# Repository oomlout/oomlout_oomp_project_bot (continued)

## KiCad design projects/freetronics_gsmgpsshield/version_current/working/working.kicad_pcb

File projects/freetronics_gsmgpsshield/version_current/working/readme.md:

# GSMGPSShield by freetronics  
This is a harvested standardized copy of a project from github.  
The original project can be found at:  
https://github.com/freetronics/GSMGPSShield  
Please consult that link for additional, details, files, and license information.  
Note: It was auto harvested and if the original repo had more than one board file or anything out of the ordinary the files here are likely not representative.

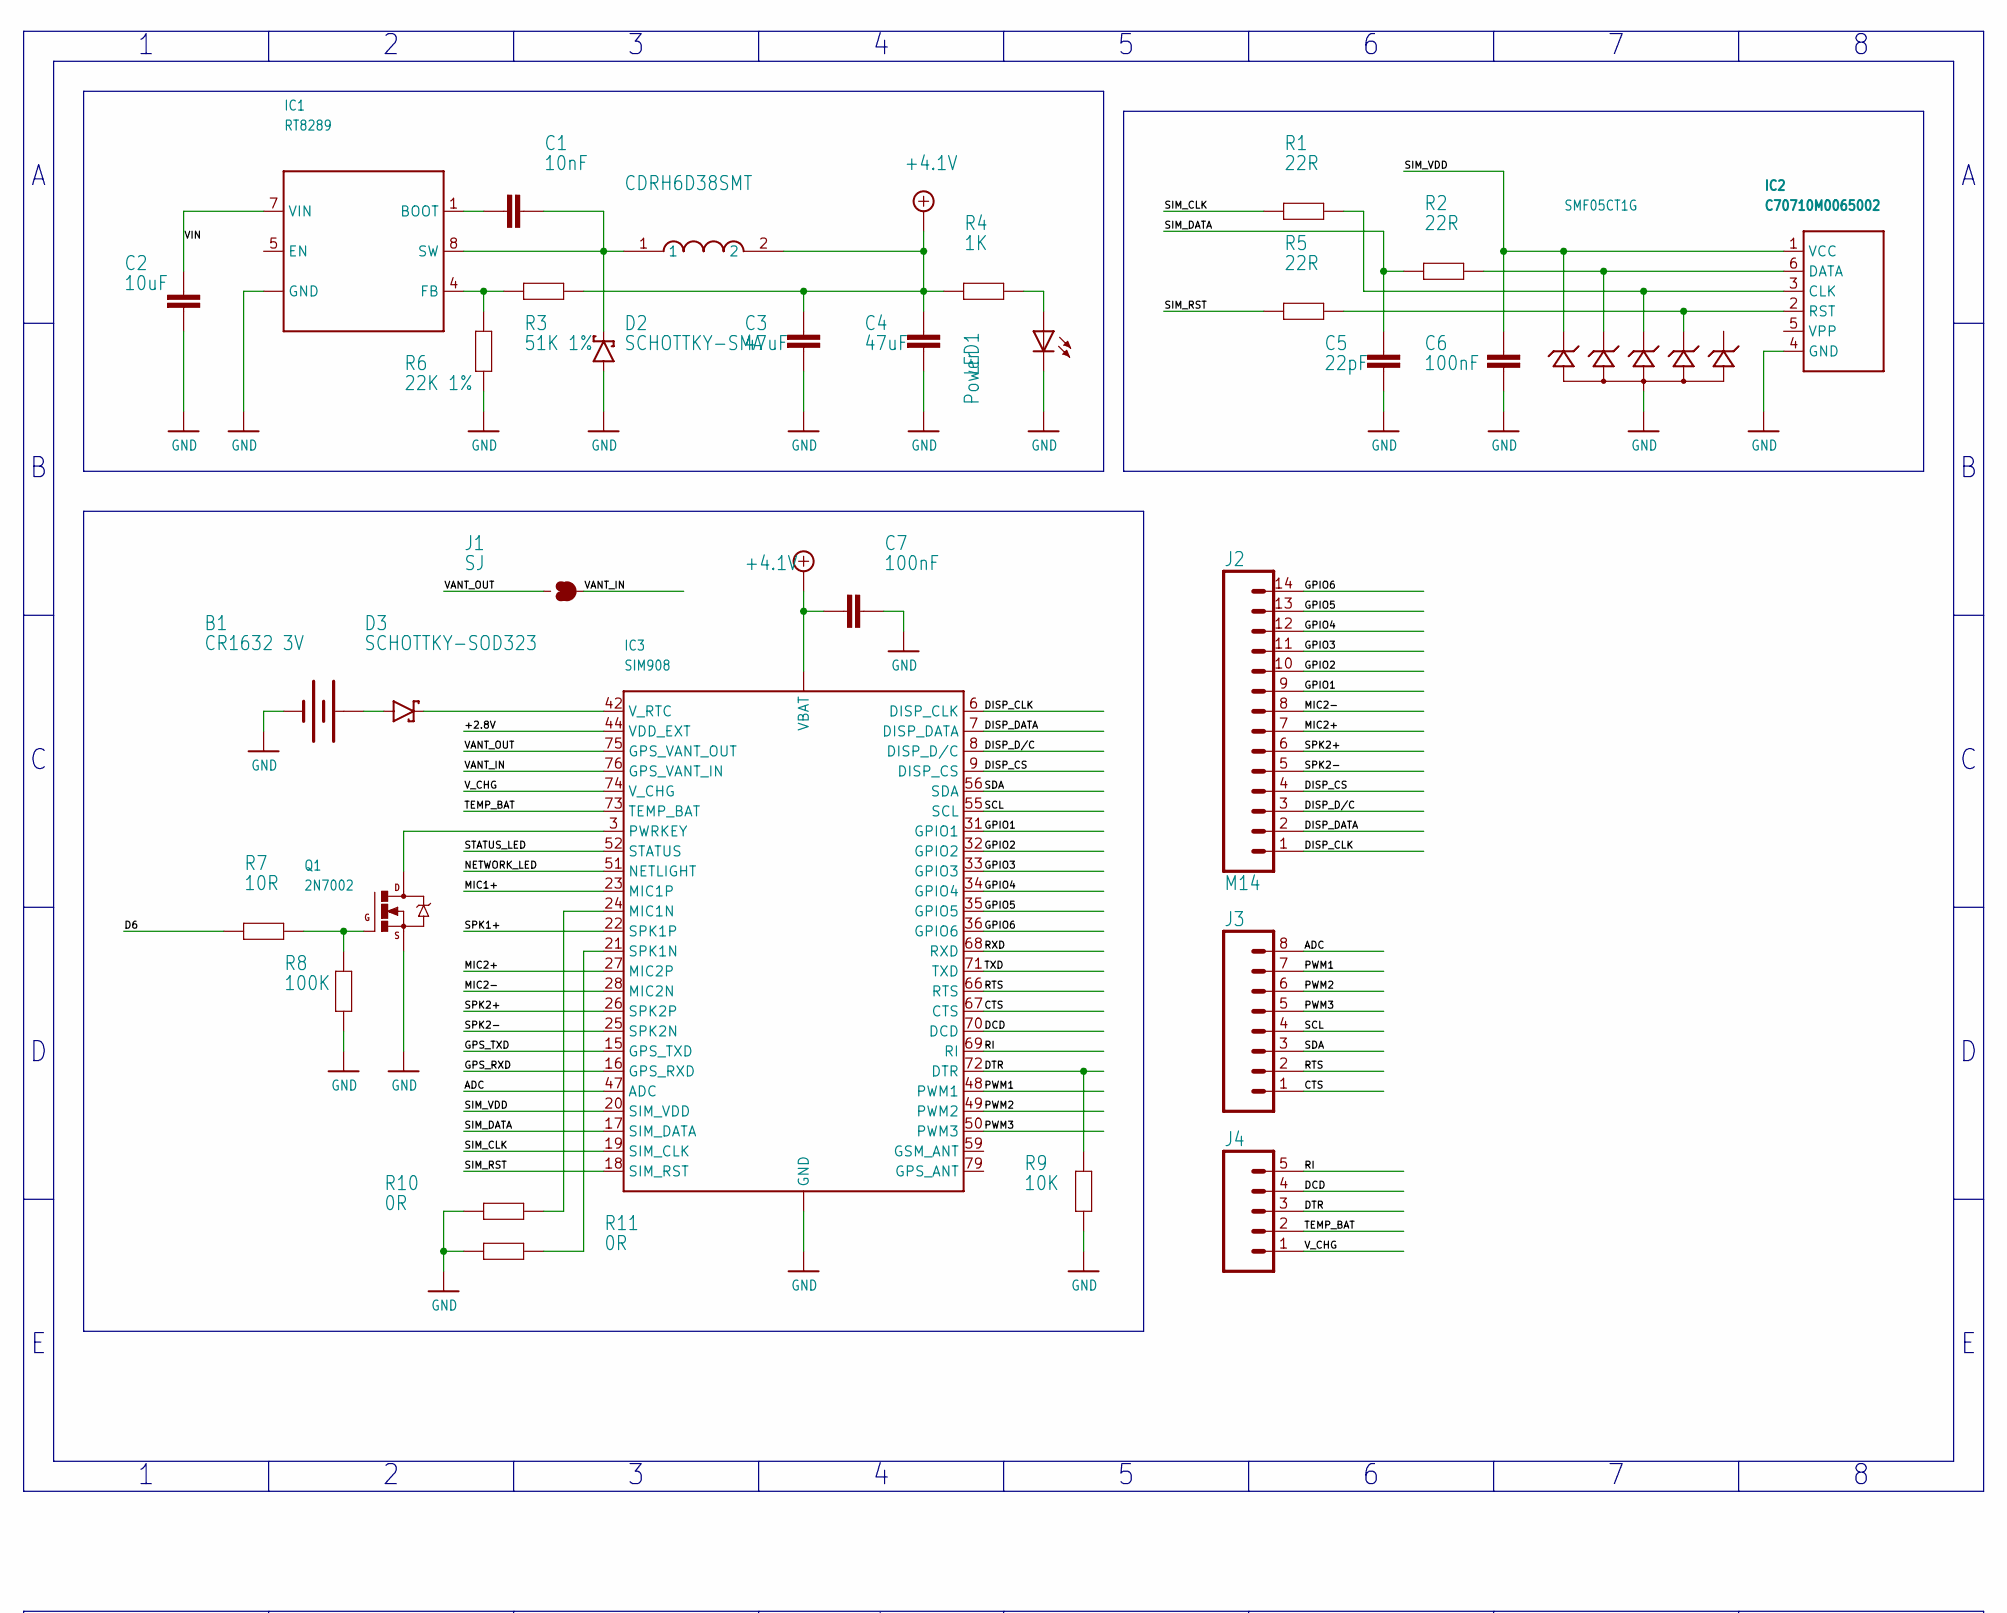
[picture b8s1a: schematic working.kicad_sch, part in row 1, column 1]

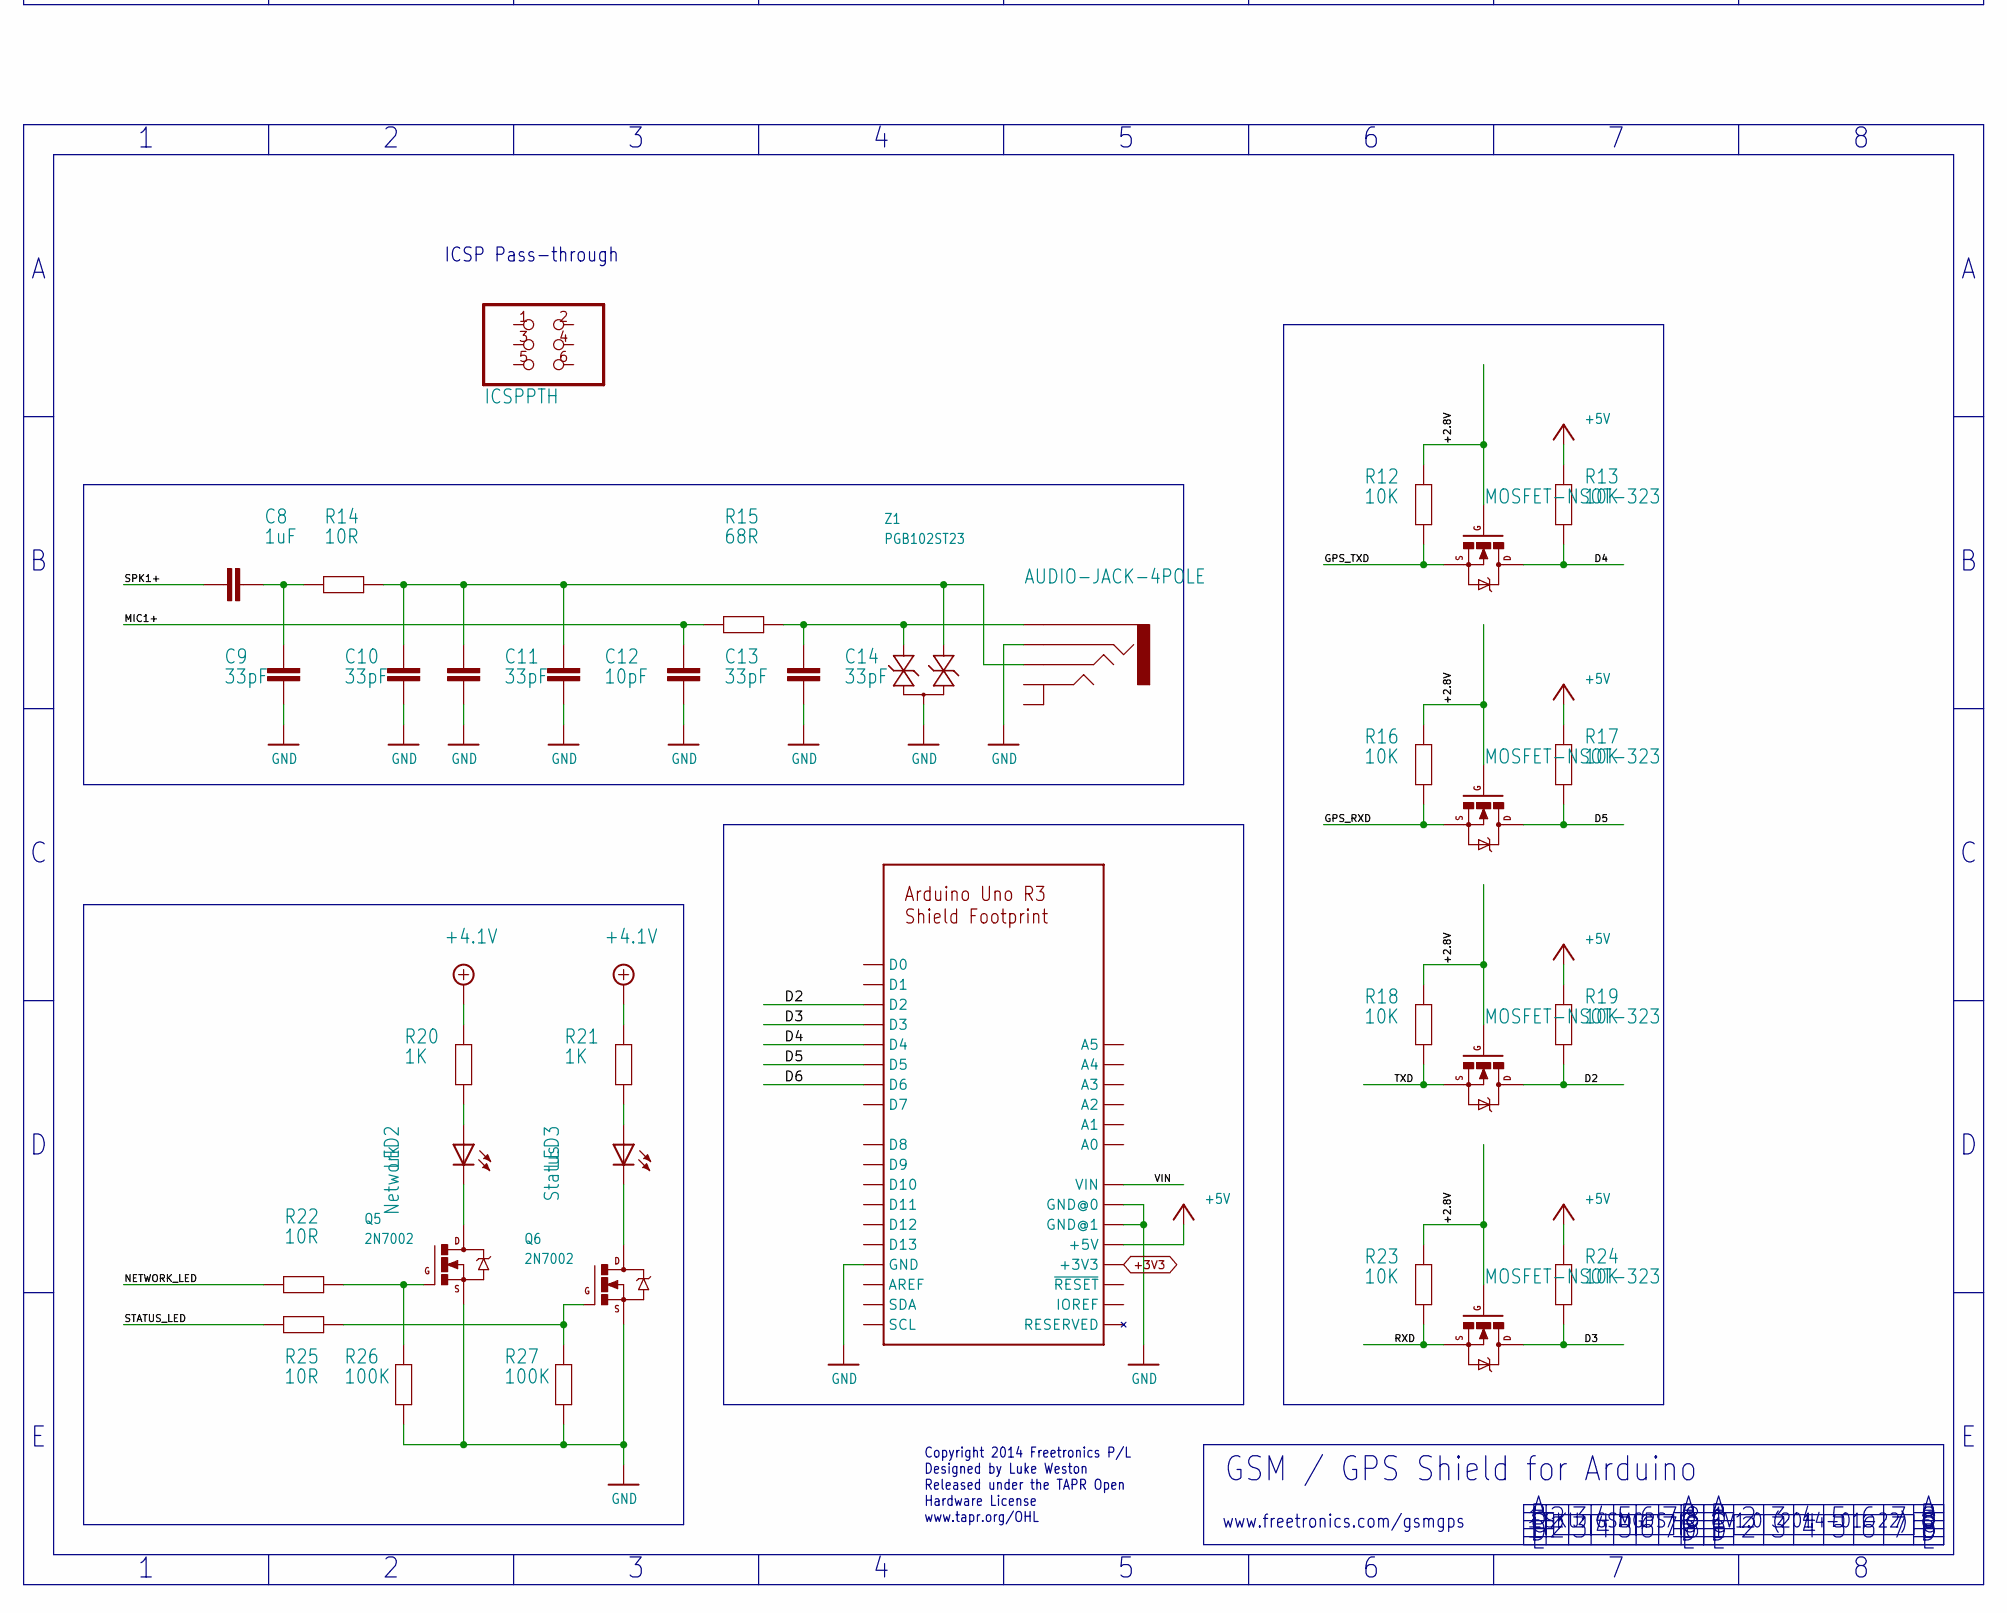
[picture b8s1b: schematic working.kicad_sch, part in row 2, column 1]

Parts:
B1: CR1632 3V; BATCON_16MM
C1: 10nF; 0603
C2: 10uF; C1206; VOLTAGE 35V
C3, C4: 47uF; C1206; VOLTAGE 10V
C5: 22pF; 0603
C6, C7: 100nF; 0603
C8: 1uF; 0603
C9, C10, C11, C13, C14: 33pF; 0603
C12: 10pF; 0603
D1: SMF05CT1G; SC70-6
D2: SCHOTTKY-SMA; SMA
D3: SCHOTTKY-SOD323; SOD-323
IC1: RT8289; SO08T
IC2: C70710M0065002
IC3: SIM908
J1: SJ
J2: M14; 1X14
J3: M08STD; 1X08
J4: M05PTH; 1X05
J5: ARDUINO-SHIELD_R3_NOISP
J6: ICSPPTH; 2X03PTH
L1: CDRH6D38SMT; CDRH
LED1: Power; LED-0603
LED2: Network; LED-0603
LED3: Status; LED-0603
Q1, Q5, Q6: 2N7002; SOT23-3
Q2, Q3, Q4, Q7: MOSFET-NSOT-323; SOT32-3
R1, R2, R5: 22R; 0603
R3: 51K 1%; 0603
R4, R20, R21: 1K; 0603
R6: 22K 1%; 0603
R7, R14, R22, R25: 10R; 0603
R8, R26, R27: 100K; 0603
R9, R12, R13, R16, R17, R18, R19, R23, R24: 10K; 0603
R10, R11: 0R; 0603
R15: 68R; 0603
S1: AUDIO-JACK-4POLE; 4UCON-18899
Z1: PGB102ST23; SOT23-3

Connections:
+2.8V: IC3.44 (VDD_EXT), Q2.1 (G), Q3.1 (G), Q4.1 (G), Q7.1 (G), R12.1, R16.1, R18.1, R23.1
+3V3: J5.3V3 (+3V3)
+4.0V: C3.1, C4.1, C7.2, IC3.62 (VBAT), IC3.63 (VBAT), L1.2, R3.1, R4.1, R20.1, R21.1
+5V: J5.+5V, R13.1, R17.1, R19.1, R24.1
ADC: IC3.47 (ADC), J3.8
CTS: IC3.67 (CTS), J3.1
D2: J5.D2, Q4.3 (D), R19.2
D3: J5.D3, Q7.3 (D), R24.2
D4: J5.D4, Q2.3 (D), R13.2
D5: J5.D5, Q3.3 (D), R17.2
D6: J5.D6, R7.2
DCD: IC3.70 (DCD), J4.4
DISP_CLK: IC3.6 (DISP_CLK), J2.1
DISP_CS: IC3.9 (DISP_CS), J2.4
DISP_D/C: IC3.8 (DISP_D/C), J2.3
DISP_DATA: IC3.7 (DISP_DATA), J2.2
DTR: IC3.72 (DTR), J4.3, R9.1
GND: B1.GND (-), C2.2, C3.2, C4.2, C5.1, C6.1, C7.1, C9.1, C10.1, C11.1, C12.1, C13.1, C14.1, D1.2 (A2), D2.A, IC1.2 (GND), IC1.3 (GND), IC1.6 (GND), IC1.PAD (GND), IC2.4 (GND), IC3.1 (GND), IC3.2 (GND), IC3.5 (GND), IC3.10 (GND), IC3.14 (GND), IC3.37 (GND), IC3.40 (GND), IC3.41 (GND), IC3.43 (GND), IC3.57 (GND), IC3.58 (GND), IC3.60 (GND), IC3.61 (GND), IC3.64 (GND), IC3.65 (GND), IC3.77 (GND), IC3.78 (GND), IC3.80 (GND), J5.GND, J5.GND@0, J5.GND@1, LED1.C, Q1.2 (S), Q5.2 (S), Q6.2 (S), R6.1, R8.1, R9.2, R10.2, R11.2, R26.1, R27.1, S1.4, Z1.3
GPIO1: IC3.31 (GPIO1), J2.9
GPIO2: IC3.32 (GPIO2), J2.10
GPIO3: IC3.33 (GPIO3), J2.11
GPIO4: IC3.34 (GPIO4), J2.12
GPIO5: IC3.35 (GPIO5), J2.13
GPIO6: IC3.36 (GPIO6), J2.14
GPS_RXD: IC3.16 (GPS_RXD), Q3.2 (S), R16.2
GPS_TXD: IC3.15 (GPS_TXD), Q2.2 (S), R12.2
MIC1+: C13.2, IC3.23 (MIC1P), R15.1
MIC2+: IC3.27 (MIC2P), J2.7
MIC2-: IC3.28 (MIC2N), J2.8
unnamed: LED1.A, R4.2
unnamed: LED2.C, Q5.3 (D)
unnamed: LED3.C, Q6.3 (D)
unnamed: Q5.1 (G), R22.1, R26.2
unnamed: Q6.1 (G), R25.1, R27.2
unnamed: D3.K, IC3.42 (V_RTC)
unnamed: IC3.3 (PWRKEY), Q1.3 (D)
unnamed: B1.PWR@1 (+), D3.A
unnamed: IC3.21 (SPK1N), R11.1
unnamed: IC3.24 (MIC1N), R10.1
unnamed: D1.5 (K5), IC2.2 (RST), R5.1
unnamed: D1.4 (K4), IC2.3 (CLK), R1.1
unnamed: D1.3 (K3), IC2.6 (DATA), R2.1
unnamed: C14.2, R15.2, S1.1, Z1.2
unnamed: C10.2, C11.2, C12.2, R14.2, S1.3, Z1.1
unnamed: C8.1, C9.2, R14.1
unnamed: Q1.1 (G), R7.1, R8.2
unnamed: LED3.A, R21.2
unnamed: LED2.A, R20.2
unnamed: C1.1, D2.K, IC1.8 (SW), L1.1
unnamed: IC1.4 (FB), R3.2, R6.2
unnamed: C1.2, IC1.1 (BOOT)
NETWORK_LED: IC3.51 (NETLIGHT), R22.2
PWM1: IC3.48 (PWM1), J3.7
PWM2: IC3.49 (PWM2), J3.6
PWM3: IC3.50 (PWM3), J3.5
RI: IC3.69 (RI), J4.5
RTS: IC3.66 (RTS), J3.2
RXD: IC3.68 (RXD), Q7.2 (S), R23.2
SCL: IC3.55 (SCL), J3.4
SDA: IC3.56 (SDA), J3.3
SIM_CLK: IC3.19 (SIM_CLK), R1.2
SIM_DATA: C5.2, IC3.17 (SIM_DATA), R2.2
SIM_RST: IC3.18 (SIM_RST), R5.2
SIM_VDD: C6.2, D1.1 (K1), IC2.1 (VCC), IC3.20 (SIM_VDD)
SPK1+: C8.2, IC3.22 (SPK1P)
SPK2+: IC3.26 (SPK2P), J2.6
SPK2-: IC3.25 (SPK2N), J2.5
STATUS_LED: IC3.52 (STATUS), R25.2
TEMP_BAT: IC3.73 (TEMP_BAT), J4.2
TXD: IC3.71 (TXD), Q4.2 (S), R18.2
VANT_IN: IC3.76 (GPS_VANT_IN), J1.2
VANT_OUT: IC3.75 (GPS_VANT_OUT), J1.1
VIN: C2.1, IC1.7 (VIN), J5.VIN
V_CHG: IC3.74 (V_CHG), J4.1

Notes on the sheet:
ICSP Pass-through
Copyright 2014 Freetronics P/L Designed by Luke Weston Released under the TAPR Open Hardware License www.tapr.org/OHL
GSM / GPS Shield for Arduino
SKU: GSMGPS
V1.0 (2014-01-22)
www.freetronics.com/gsmgps

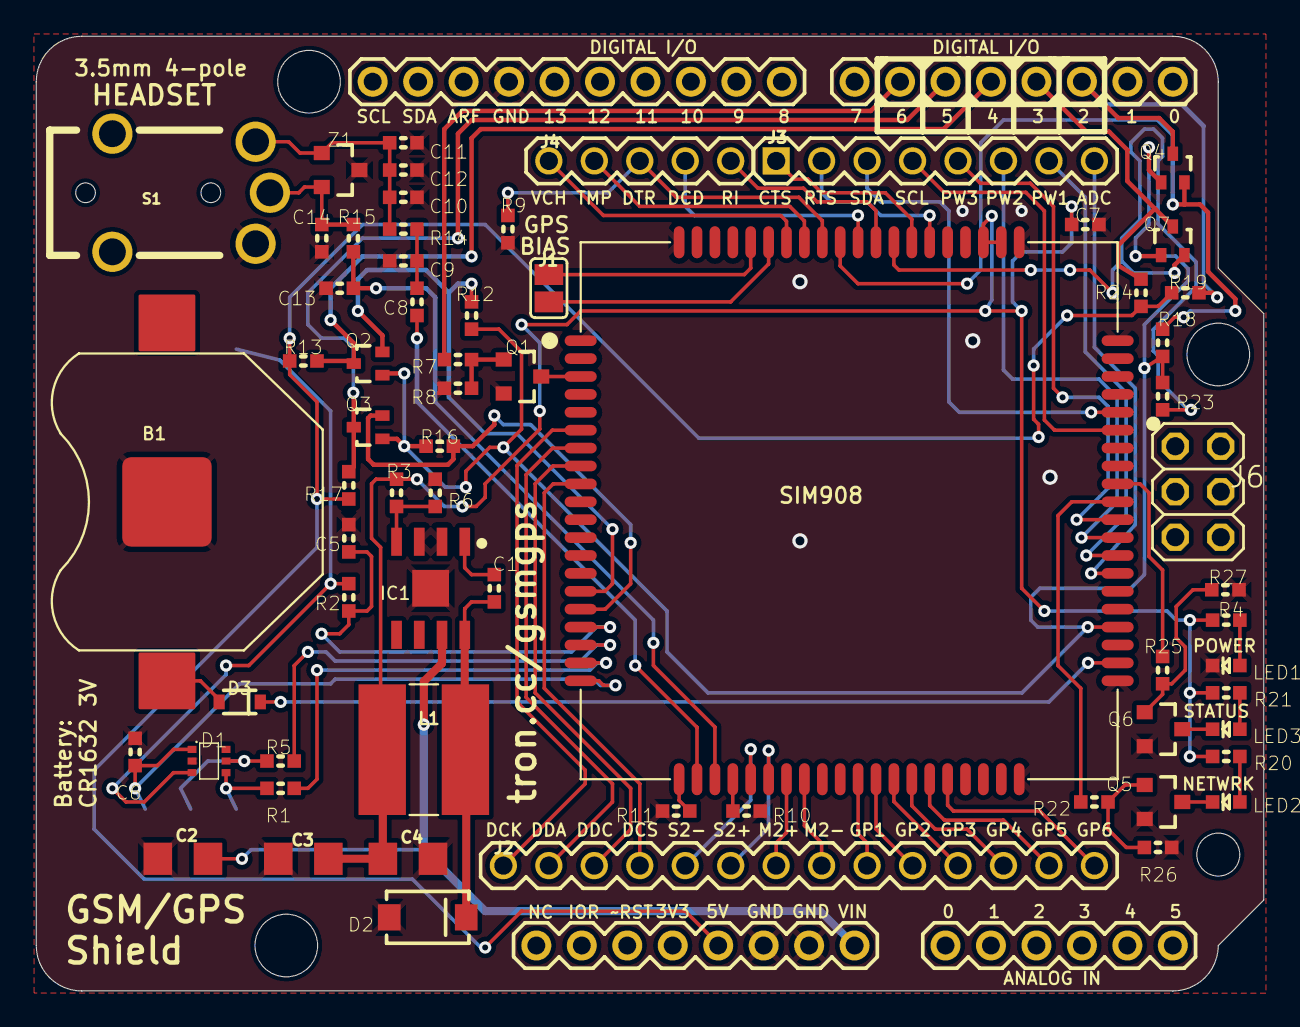
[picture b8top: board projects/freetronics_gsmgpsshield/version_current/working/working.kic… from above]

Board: 2 copper layers, 68.6 x 53.3 mm, 67 parts (1 on the bottom side), 73 nets.

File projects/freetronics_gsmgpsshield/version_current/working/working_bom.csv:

"Id";"Designator";"Footprint";"Quantity";"Designation";"Supplier and ref";
1;"C14,C10,C9,C13,C11";"0603";5;"33pF";;;
2;"R1,R2,R5";"0603";3;"22R";;;
3;"R14,R25,R7,R22";"0603";4;"10R";;;
4;"C4,C3";"C1206";2;"47uF";;;
5;"Q2,Q4,Q3,Q7";"SOT32-3";4;"RJU003N03 N-MOSFET";;;
6;"C6,C7";"0603";2;"100nF";;;
7;"R15";"0603";1;"68R";;;
8;"R27,R26,R8";"0603";3;"100K";;;
9;"R20,R21,R4";"0603";3;"1K";;;
10;"Q1,Q5,Q6";"SOT23-3";3;"2N7002";;;
11;"R9,R18,R24,R19,R12,R13,R23,R16,R17";"0603";9;"10K";;;
12;"D2";"SMA";1;"B340A-13-F";;;
13;"R11,R10";"0603";2;"0R";;;
14;"C5";"0603";1;"22pF";;;
15;"R3";"0603";1;"51K 1%";;;
16;"L1";"CDRH";1;"10uH";;;
17;"LED3";"LED-0603";1;"Status";;;
18;"J3";"1X08";1;"";;;
19;"R6";"0603";1;"22K 1%";;;
20;"C8";"0603";1;"1uF";;;
21;"J1";"SJ";1;"Active GPS Antenna Bias";;;
22;"D1";"SC70-6";1;"SMF05CT1G";;;
23;"LED1";"LED-0603";1;"Power";;;
24;"IC3";"SIM908";1;"SIM908";;;
25;"J2";"1X14";1;"";;;
26;"LED2";"LED-0603";1;"Network";;;
27;"IC1";"SO08T";1;"RT8289";;;
28;"D3";"SOD-323";1;"NSR0340HT1G";;;
29;"J4";"1X05";1;"";;;
30;"B1";"BATCON_16MM";1;"CR1632 3V";;;
31;"S1";"4UCON-18899";1;"4UCON-18899";;;
32;"J6";"2X03PTH";1;"ICSPPTH";;;
33;"C12";"0603";1;"10pF";;;
34;"C2";"C1206";1;"10uF";;;
35;"Z1";"SOT23-3";1;"PGB102ST23";;;
36;"C1";"0603";1;"10nF";;;
37;"J5";"ARDUINO-SHIELD_R3_NOISP";1;"ARDUINO-SHIELD_R3_NOISP";;;
38;"IC2";"C70710M0065002";1;"C70710M0065002";;;
